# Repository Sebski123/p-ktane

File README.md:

# P-KTANE
## Sources
* https://github.com/dlareau/KTANE-physical
* https://imgur.com/gallery/J6HdM0v
* https://old.reddit.com/r/ktane/comments/a3fgyt/i_made_a_physical_version_of_the_video_game_keep/

run command `git config --local --add diff.fcinfo.textconv ./MiscCode/fcinfo` to use git diff on FreeCAD files

## ReDesign
### To-do
- [ ] Rewrite SWire protocol
- - [ ] Expand addressing (allow multiple of same module)
- - [ ] Don't need adress in packet
- - [ ] Don't to send 'ack' message (built into i2c)
- - [ ] Don't start and end messages (built into i2c)
- - [ ] Update sigrok decoder with new protocol
- [ ] Decide on module size
- [x] Add pinheaders to all schematics
- [ ] Figure out how to add battery/indicators
- [ ] Make symbol/footprint for arcade button
- [ ] Redo SimonSays schematic with above symbol
- [ ] Design PCBs
- [ ] Make more modules
- [x] Organize Repo
- [ ] Clean up README
- [x] Choose which modules to build
- [ ] Double check value of RSet for MAX7219 ICs
- [ ] Figure out how to add radio dial to MorseCode
- [ ] Modules on back?
- [ ] Add presets from KTANE?
- [ ] Variable amount of strikes?
- [ ] Use 14-segments for strike indicator?
- [ ] Better leaderboard?
- [ ] Way to enter name? (Password module?)
- [ ] Better system for swapping modules?
- [ ] Use HD107S for button module?
- [ ] Use built-in resistor to identify button?
- [ ] Implement Bounce2 in all button modules
- [ ] Add pullup resistors to I2C bus
- [ ] Make e-paper display
  - [x] Expose PSU enable pin
  - [x] Add SRAM IC
  - [x] Add microSD slot?
  - [ ] White image for storage
  - [ ] Add display/controller to GxEPD2?
- [ ] Figure out how to power device
  - [ ] Wired?
  - [ ] Battery?
  - [ ] Both?
- [ ] Add protection circuits?
  - [ ] Short circuit protection?
  - [ ] Overvoltage protection
    - [ ] Zener diode voltage clamp
  - [ ] Overcurrent protection
    - [x] Add polyfuse to every module
    - [ ] Measure curent draw for each module
- [ ] Add TMRpcm and SD to timer?
  - [ ] [This](https://maxoffsky.com/maxoffsky-blog/how-to-play-wav-audio-files-with-arduino-uno-and-microsd-card/)
  - [ ] Or [this](https://circuitdigest.com/microcontroller-projects/arduino-audio-music-player)

### v1 Compromises
| Module       | Problem                                              | Possible solution                              |
|--------------|------------------------------------------------------|------------------------------------------------|
| Button       | Text is separate from button instead of on top       | 3D-print text on button                        |
| Button       | Text is reduced to a single digit                    | Use changeable buttons with 3D-printed text    |
| Edgework     | Serial number is rough (16-segment display)          | Use E-paper display                            |
| Edgework     | All possible indicators are always present           | Use E-paper displays (expensive)               |
| Maze         | Hard to differentiate elements                       | Use RGB led's on PCB                           |
| Maze         | No way to see maze walls                             | Use 11x11 grid to also show walls              |
| Memory       | Press button under display instead of display itself | Place button under display and make it movable |
| Simon Says   | Rough sound                                          | Replace buzzer with proper speaker             |
| Simon Says   | Rough sound                                          | Replace tone() with better sine wave (filter?) |
| Simple wires | Wires are unplugged instead of cut                   | Use magnets to "cut" wires                     |

## Modules
| Module                                                       |Going to build| Coded | Schematic | PCB | Parts | Tested | Built | I2C addr.|
|--------------------------------------------------------------|--------------|-------|---------- |-----|-------|--------|-------|----------|
| Timer (Controller)                                           |      ✔️     |   🟡  |    🟡    |  ❌ |  ❌  |   ❌   |  ❌  |  MASTER  |
| Config (ESP8266)                                             |      ✔️     |   🟡  |    ✔️    |  ❌ |  ✔️  |   ✔️   |  ❌  |    0x1   |
| [Button](https://i.imgur.com/Leew7du.png)                    |      ✔️     |   ✔️  |    ✔️    |  ❌ |  ❌  |   ❌   |  ❌  |    0x2   |
| [Complicated Wires](https://i.imgur.com/jJb2Kp9.png)         |      ✔️     |   ✔️  |    ✔️    |  ❌ |  ❌  |   ❌   |  ❌  |    0x3   |
| [Maze](https://i.imgur.com/xXMdvLr.png)                      |      ✔️     |   🟡  |    ✔️    |  ❌ |  🟡  |   ❌   |  ❌  |    0x4   |
| [Memory](https://i.imgur.com/bvGt5gz.png)                    |      ✔️     |   🟡  |    ✔️    |  🟡 |  ❌  |   ❌   |  ❌  |    0x5   |
| [Morse Code](https://i.imgur.com/V4XAdVZ.png)                |      ✔️     |   ❌  |    🟡    |  ❌ |  ❌  |   ❌   |  ❌  |    0x6   |
| [Needy Capacitor Discharge](https://i.imgur.com/Q0VJkoo.png) |      ✔️     |   ✔️  |    ✔️    |  ❌ |  ❌  |   ❌   |  ❌  |    0x7   |
| [Needy Knob](https://i.imgur.com/hlpkEUD.png)                |      ✔️     |   ✔️  |    ✔️    |  ❌ |  ❌  |   ❌   |  ❌  |    0x8   |
| [Needy Venting Gas](https://i.imgur.com/f2eua3p.png)         |      ✔️     |   ✔️  |    ✔️    |  ❌ |  ❌  |   ❌   |  ❌  |    0x9   |
| [Password](https://i.imgur.com/us0XRBs.png)                  |      ✔️     |   ❌  |    ✔️    |  ❌ |  ❌  |   ❌   |  ❌  |    0xA   | 
| [Simon Says](https://i.imgur.com/uX7BzED.png)                |      ✔️     |   🟡  |    ✔️    |  ❌ |  ❌  |   ❌   |  ❌  |    0xB   |
| [Simple Wires](https://i.imgur.com/xLXpCYH.png)              |      ✔️     |   🟡  |    ✔️    |  ❌ |  ❌  |   ❌   |  ❌  |    0xC   |
| [Keypads](https://i.imgur.com/Zy6ScEo.png)                   |      ❌     |   ❌  |    ❌    |  ❌ |  ❌  |   ❌   |  ❌  |    N/A   |
| [Who's on First](https://i.imgur.com/YisE1go.png)            |      ❌     |   ❌  |    ❌    |  ❌ |  ❌  |   ❌   |  ❌  |    N/A   |
| [Wire Sequence](https://i.imgur.com/1drzKTO.png)             |      ❌     |   ❌  |    ❌    |  ❌ |  ❌  |   ❌   |  ❌  |    N/A   |

# How to burn bootloader and upload sketches for ATMega328
## How to burn bootloader
### Install boards
1. Open the Arduino IDE.
1. Open the **File > Preferences** menu item.
1. Enter the following URL in **Additional Boards Manager URLs**:

    ```
    https://mcudude.github.io/MiniCore/package_MCUdude_MiniCore_index.json
    ``` 

1. Open the **Tools > Board > Boards Manager...** menu item.
1. Wait for the platform indexes to finish downloading.
1. Scroll down until you see the **MiniCore** entry and click on it.
1. Click **Install**.
1. After installation is complete close the **Boards Manager** window.
1. **Note**: If you plan to use the *PB series, you need the latest version of the Arduino toolchain. This toolchain is available through IDE 1.8.6 or newer. Here's how you install/enable the toolchain:
  -  Open the **Tools > Board > Boards Manager...** menu item.
  -  Wait for the platform indexes to finish downloading.
  -  The top is named **Arduino AVR boards**. Click on this item.
  -  Make sure the latest version is installed and selected
  -  Close the **Boards Manager** window.

### Prepare Arduino
1. Copy [this](https://raw.githubusercontent.com/adafruit/ArduinoISP/master/ArduinoISP.ino) code into the Arduino IDE and upload it to an Arduino normally.
1. Connect Arduino to the ATMega as shown below (Capacitor is important).

### Burn bootloader
1. Select the **Tools > Board > ATmega328** menu item from the MiniCore section.
1. Select the **Tools > Variant > 328 / 328A** menu item.
1. Select the **Tools > Clock > Internal 8MHz** menu item.
1. Select the **Tools > Programmer > Arduino as ISP** menu item.
1. Click **Tools > Burn Bootloader**

## How to upload sketches
### Wiring
1. Remove ATmega328 from Arduino
1. Connect Arduino to the ATMega as shown below.

### Uploading
1. Select the **Tools > Board > ATmega328** menu item from the MiniCore section.
1. Select the **Tools > Variant > 328 / 328A** menu item.
1. Select the **Tools > Clock > Internal 8MHz** menu item.
1. Select the **Tools > Programmer > Arduino as ISP** menu item.
1. Click Upload.

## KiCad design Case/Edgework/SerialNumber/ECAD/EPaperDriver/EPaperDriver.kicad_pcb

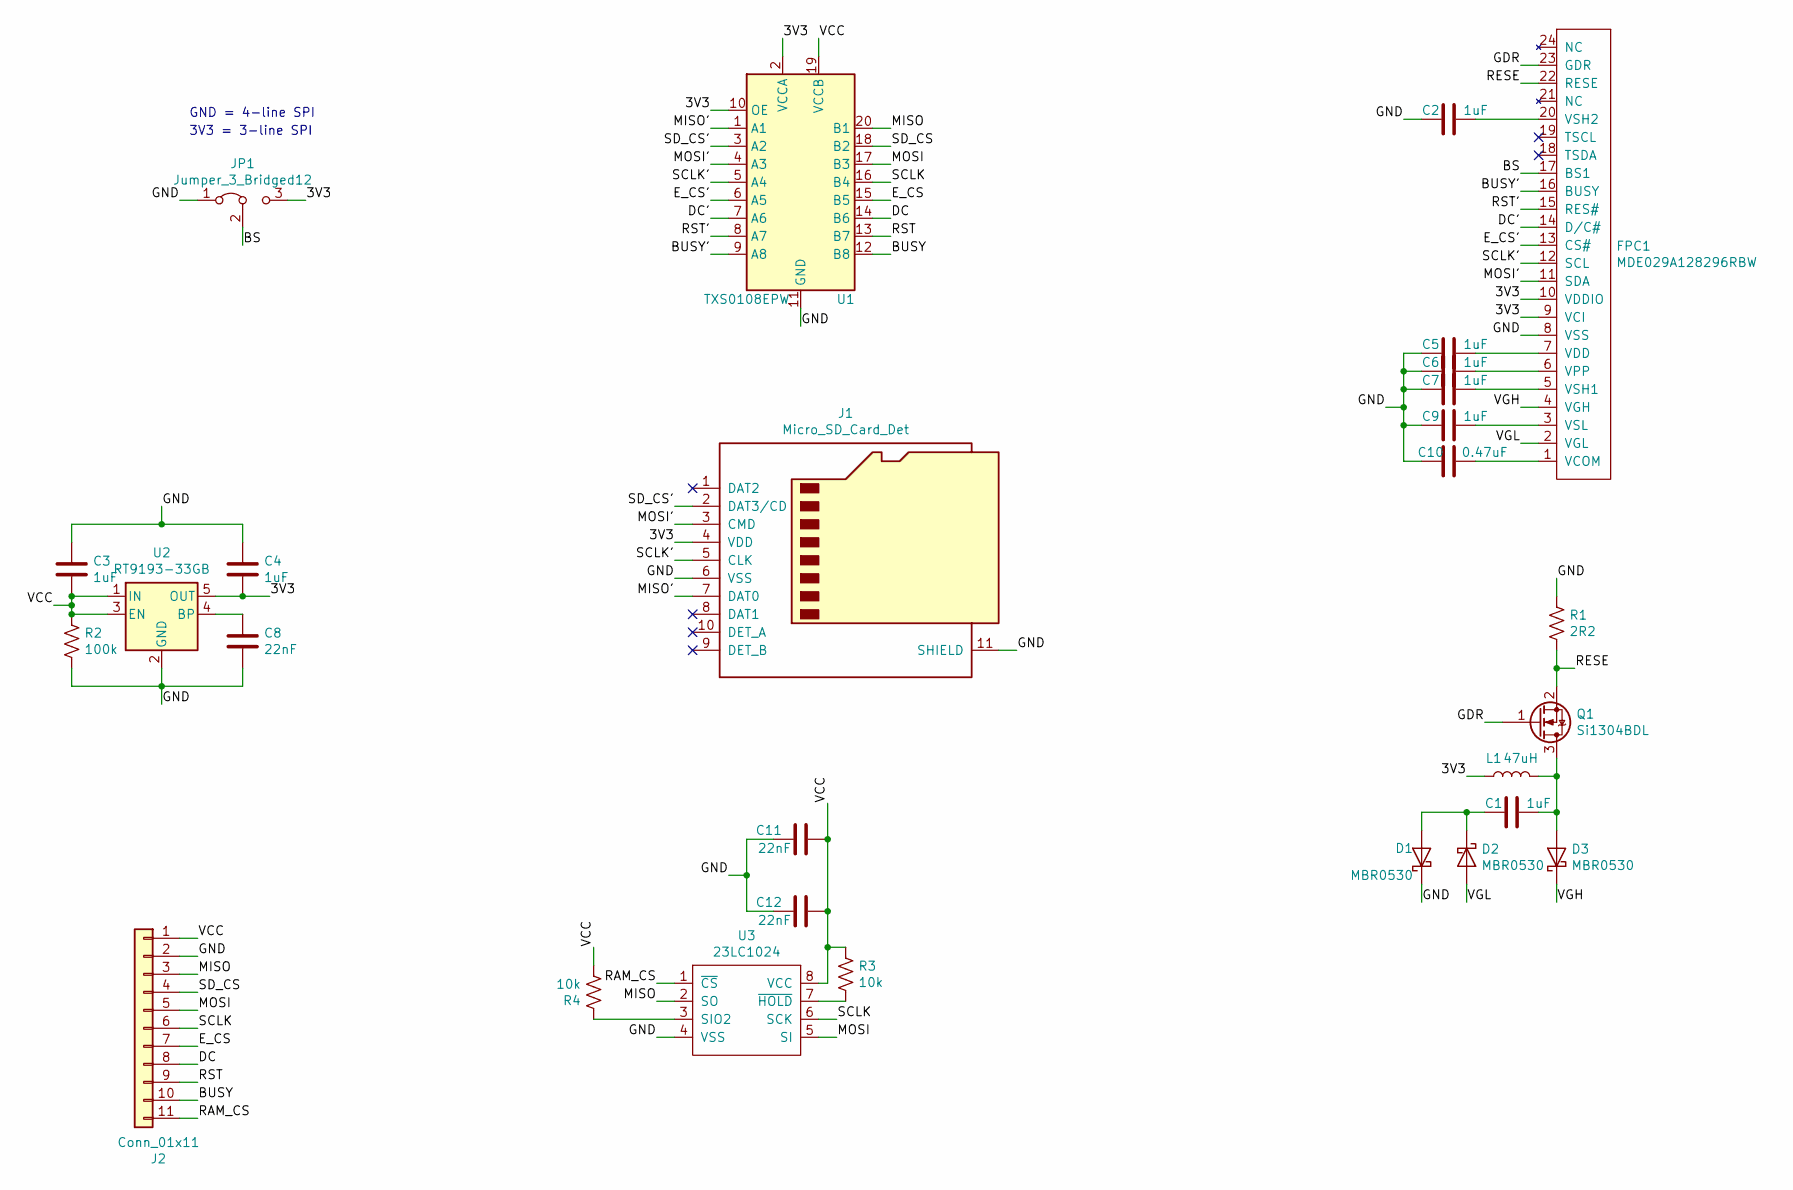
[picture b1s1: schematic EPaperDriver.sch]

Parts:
C1, C2, C3, C4, C5, C6, C7, C9: 1uF; C_0805_2012Metric_Pad1.15x1.40mm_HandSolder
C8, C11, C12: 22nF; C_0805_2012Metric_Pad1.15x1.40mm_HandSolder
C10: 0.47uF; C_0805_2012Metric_Pad1.15x1.40mm_HandSolder
D1, D2, D3: MBR0530; D_SOD-123
FPC1: MDE029A128296RBW; Hirose_FH12-24S-0.5SH_1x24-1MP_P0.50mm_Horizontal
J1: Micro_SD_Card_Det; microSD_HC_Hirose_DM3D-SF
J2: Conn_01x11; PinHeader_1x11_P2.54mm_Vertical
JP1: Jumper_3_Bridged12; SolderJumper-3_P1.3mm_Open_Pad1.0x1.5mm
L1: 47uH; L_12x12mm_H6mm
Q1: Si1304BDL; SOT-323_SC-70
R1: 2R2; R_0805_2012Metric_Pad1.15x1.40mm_HandSolder
R2: 100k; R_0805_2012Metric_Pad1.15x1.40mm_HandSolder
R3, R4: 10k; R_0805_2012Metric_Pad1.15x1.40mm_HandSolder
U1: TXS0108EPW; TSSOP-20_4.4x6.5mm_P0.65mm
U2: RT9193-33GB; SOT-23-5
U3: 23LC1024; SOIC-8_3.9x4.9mm_P1.27mm

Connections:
/3V3: C4.2, FPC1.9 (VCI), FPC1.10 (VDDIO), J1.4 (VDD), JP1.3 (B), L1.1, U1.2 (VCCA), U1.10 (OE), U2.5 (OUT)
/BS: FPC1.17 (BS1), JP1.2 (C)
/BUSY: J2.10, U1.12 (B8)
/BUSY': FPC1.16 (BUSY), U1.9 (A8)
/DC: J2.8, U1.14 (B6)
/DC': FPC1.14 (D/C#), U1.7 (A6)
/E_CS: J2.7, U1.15 (B5)
/E_CS': FPC1.13 (CS#), U1.6 (A5)
/GDR: FPC1.23 (GDR), Q1.1 (G)
/GND: C2.1, C3.1, C4.1, C5.1, C6.1, C7.1, C8.2, C9.1, C10.1, C11.1, C12.1, D1.1 (K), FPC1.8 (VSS), J1.6 (VSS), J1.11 (SHIELD), J2.2, JP1.1 (A), R1.1, R2.2, U1.11 (GND), U2.2 (GND), U3.4 (VSS)
/MISO: J2.3, U1.20 (B1), U3.2 (SO)
/MISO': J1.7 (DAT0), U1.1 (A1)
/MOSI: J2.5, U1.17 (B3), U3.5 (SI)
/MOSI': FPC1.11 (SDA), J1.3 (CMD), U1.4 (A3)
/RAM_CS: J2.11, U3.1 (~CS~)
/RESE: FPC1.22 (RESE), Q1.2 (S), R1.2
/RST: J2.9, U1.13 (B7)
/RST': FPC1.15 (RES#), U1.8 (A7)
/SCLK: J2.6, U1.16 (B4), U3.6 (SCK)
/SCLK': FPC1.12 (SCL), J1.5 (CLK), U1.5 (A4)
/SD_CS: J2.4, U1.18 (B2)
/SD_CS': J1.2 (DAT3/CD), U1.3 (A2)
/VCC: C3.2, C11.2, C12.2, J2.1, R2.1, R3.1, R4.2, U1.19 (VCCB), U2.1 (IN), U2.3 (EN), U3.8 (VCC)
/VGH: D3.1 (K), FPC1.4 (VGH)
/VGL: D2.2 (A), FPC1.2 (VGL)
unnamed: C1.1, D3.2 (A), L1.2, Q1.3 (D)
unnamed: C1.2, D1.2 (A), D2.1 (K)
unnamed: C2.2, FPC1.20 (VSH2)
unnamed: C5.2, FPC1.7 (VDD)
unnamed: C6.2, FPC1.6 (VPP)
unnamed: C7.2, FPC1.5 (VSH1)
unnamed: C8.1, U2.4 (BP)
unnamed: C9.2, FPC1.3 (VSL)
unnamed: C10.2, FPC1.1 (VCOM)
unnamed: R3.2, U3.7 (~HOLD~)
unnamed: R4.1, U3.3 (SIO2)

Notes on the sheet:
GND = 4-line SPI
3V3 = 3-line SPI

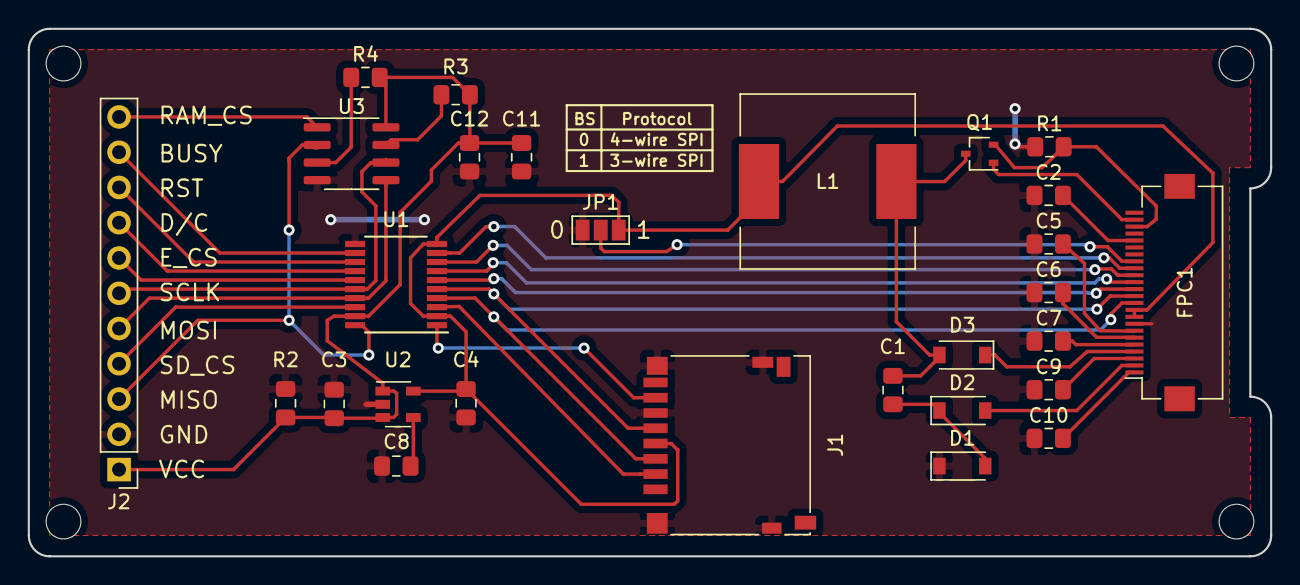
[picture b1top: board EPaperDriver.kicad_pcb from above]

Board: 4 copper layers, 89.5 x 38.0 mm, 28 parts (0 on the bottom side), 36 nets.

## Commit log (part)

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2019-08-02 Moved and renamed some files
2019-08-02 Added updated .ino file
2019-08-02 Fixed typo
2019-08-02 Started work on maze code
2019-08-05 Fixed win/lose condition
2019-08-05 Added config module code
2019-08-05 Made strikes and clear LED work + serial from ESP
2019-08-05 Renamed folder
2019-08-06 Updated missing parts list
2019-08-12 Added names to some of the components
2019-08-15 Fixing some pin numbers
2019-08-15 Finished maze Module schematic
2020-04-02 Added Arduino config
2020-04-02 Added basic wires module
2020-04-02 Rename files
2020-04-02 Added SimonSays 3d files
2020-04-02 Fixed includes
2020-04-02 Added functionality for modules to get time from controller
2020-04-02 Added button module
2020-04-06 Added some logging for debugging
2020-04-06 Added prebuild task
2020-04-07 Made code match schematics
2020-04-08 Added part file for button base
2020-04-08 Added part file for button middle
2020-04-08 Fix css on setup page
2020-04-08 Fixed formatting and added some debug messages
2020-04-08 Fixed formatting and added debugging via. SWSerial
2020-04-09 Added template for module face plate
2020-04-09 Added prototype for button face plate, not finalized yet
2020-04-09 Added section for Burning bootloader and uploading sketches
2020-04-10 Updated face plate, added ring part. Still need to make outer case for button
2020-04-11 Added spreadsheet for calculating expenses
2020-04-12 Fixed issue of dest_time overflowing
2020-04-12 Remove NeoICSerial Module
2020-04-12 Get newest commit from NeoICSerial
2020-04-12 Now keeps showing time left when bomb is solved
2020-04-12 Export schematic as pdf
2020-04-12 Revert "Added frames to all modules"
    This reverts commit 3eabf43de3682e49b345895a8346113ada920e34
2020-04-14 Modified existing face plates with wider spacings
2020-04-14 Added face plate for memory module, buttons included
2020-04-22 Changed wire face plate to the correct file
2020-04-22 changed button face plate to correct file
2020-04-26 Added missing step in upload guide
2020-04-26 Fixed issue with red and black wires being swaped and added more logging
2020-04-29 Added finished design of box
2020-04-29 Added solidworks files for each box part
2020-04-29 Updated wire face plate with larger holes
2020-04-29 Added assembly for box
2020-04-30 Added corner piece to box and updated the assembly
2020-04-30 Added new submodule for controlling a MAX6954 LED driver
2020-04-30 Added python script for decoding DSerial packages
2020-04-30 Updated schematic
2020-05-02 Added display for serial number and renamed some variables
2020-05-02 Updated MAX6954 lib
2020-05-05 Added main module face plate and speaker grill
2020-05-05 Added file for button face plate side bar
2020-05-06 Removed old 7-segment code
2020-05-11 difference got paid
2020-05-11 prebuild script should now work on other pc's
2020-05-11 Fixed red and black being swapped and added some logging
2020-05-11 Update to show what it should look like
2020-05-11 Added client number to maze module
2020-05-13 Added face plate for maze module
2020-05-14 Changed varable types to save memory
2020-05-14 Added some logging
2020-05-14 Added even more logging
2020-05-14 Moved a bunch of strings to progmem to save memory
2020-05-14 Added debounceing to buttons
2020-05-14 moved led logic inside main loop
2020-05-14 fixed formatting
2020-05-14 Updated website to support wire generation
2020-05-14 Updated maze module face plate with bigger spacings
2020-05-17 Added code for rgb leds and finished module logic
2020-05-17 Change schematic to accurately reflect how clear leds work
2020-05-18 Added buzzer to simon says module
2020-05-18 Added buzzer code to simon says
2020-05-20 Simon says will now get config from main module
2020-05-20 Switched to using LedControl lib for memory module
2020-05-20 Added some loging
2020-05-20 Fixed buttons being inverted
2020-05-20 Swapped "up" and "left" buttons
2020-05-20 Removed infinite loop that prevented module from being restarted
2020-05-21 Updated button base to have replacable legs
2020-05-21 Added files for button module support
2020-05-21 Updated modules to use SWire
2020-05-21 Started updating mainModule to use SWire
2020-05-21 Started updating KTANECommon to use SWire
2020-05-21 Update prebuild script
2020-05-22 Removed unused functions and added some logging
2020-05-22 Removed unused variables
2020-05-22 Now client at least gets config
2020-05-24 Added a bit of logging
2020-05-24 Updated I2C events for SWireClient
2020-05-24 Update identifyClients to only accept ACK as valid
2020-05-24 Add function to check for incoming messages from slaves
2020-05-24 Removed 'Y' as a possible character for serial nr to match game
2020-05-24 Now only pools clients every 100 ms
2020-05-24 Added an exception for incoming data
2020-05-25 Added functionality to free up memory
2020-05-25 Removed logging from lib
2020-05-25 Changed logging for maze module
2020-05-25 Updated maze module pins for I2C
2020-05-25 Updated simon says module pins for I2C
2020-05-25 Updated memory module pins for I2C
2020-05-25 Updated button module pins for I2C
2020-05-25 Fixed issue with display not clearing
2020-05-25 Update formatting
2020-05-25 Removed NeoICSerial lib
2020-05-25 Wires module now uses external ADC(MCP3008)
2020-05-25 Added logging for memory
2020-05-25 Updated modules for I2C and added external ADC for wires module
2020-05-25 Swapped 2 pins and added mising class init
2020-05-25 Changed submodule urls to use SSH
2020-05-25 Added Adafruit_MCP3008 lib as submodule
2020-05-25 Removed useless code
2020-05-25 Removed comment and added logging
2020-05-26 updated pillar for button holder
2020-05-26 Updated spacings for memory module face plate
2020-05-26 Update PDF with I2C schematic
2020-05-26 Added power connections for wires module
2020-05-26 Tweaked values for external ADC
2020-05-26 Added char escape for null char
2020-05-26 Added connection betwen main module and config module
2020-05-26 Removed extra '|'
2020-05-26 Fixed 2 swapped functions
2020-05-26 Increased length of stem
2020-05-26 Added part for a button holder for memory module
2020-05-27 Made logging more verbose for incomming messages
2020-05-27 Fix formatting
2020-05-27 Swapped buttons 3 and 4
2020-05-27 Uncommented test stuff
2020-05-28 Renamed simon says buttons
2020-05-29 Update MAX6954 submodule
2020-05-29 Swapped 2 pins on MAX6954 IC for readability
2020-06-01 Added template module
2020-06-01 Update submodule
2020-06-01 Fixed speaker pin being wrong
2020-06-01 Goal can no longer appear on marker locations
2020-06-05 Updated to work onESP32
2020-06-05 Updated schematic for report
2020-06-06 Fixed wires module
2020-06-07 Renamed function arguments and added function prototype
2020-06-07 Added some defines for clarity
2020-06-07 Added some logging for debuging
2020-06-07 Now properly detects when button has been held
2020-06-08 Added code for displaying millisecons
2020-06-08 Now sets all clock digits to 0
2020-06-08 Now actually displays 0's on loose
2020-06-08 Added timeout when waiting for time from main module
2020-06-08 Switched to analogWrite for better colors
2020-06-09 Fixed part being different from manual
2020-06-10 Added submodule for MCP23017 lib
2020-06-11 Added MCP23017 to schematic
2020-06-11 Added resistors to indicator led's
2020-06-11 Added code for supporting batteries and indicators
2020-06-11 Now waits for serial to be ready instead of set amount of time
2020-06-12 Added simulator for predicting solutions for all modules
2020-06-12 Buton now takes into account batteries and lit indicators
2020-06-13 Added comment
2020-06-13 Commented out unused code
2020-06-13 Can now send scores to firebase
2020-06-13 Now sends time left to ESP on win
2020-06-14 Add .gitignore entries for Firebase
2020-06-14 Fixed error on no batteries
2020-06-28 Fixed wrong comment
2020-06-28 Updated simulator
2020-08-06 Moved some stuff around
2020-08-06 Added schematic to each individual module
2020-08-06 Update prebuild task
2020-10-19 Added Adafruit_LiquidCrystal as submodule for controlling LCDs
2020-10-19 Converted button schematic to KiCad
2020-10-19 Converted config schematic to KiCad
2020-10-19 Converted simonSays schematic to KiCad
2020-10-19 Converted simpleWires schematic to KiCad
2020-10-19 Added complicatedWires schematic
2020-10-19 Added morseCode schematic
2020-10-19 Added NeedyKnob schematic
2020-10-19 Added password schematic
2020-10-19 Converted maze schematic to KiCad and swapped single color leds with RGB ones
2020-10-19 Added some update reminders
2020-10-19 Activated internal pullup resistors for buttons
2020-10-19 Added some placeholder files
2020-10-19 Updated what arduino.json should look like
2020-10-19 Added code for ComplicatedWires
2020-10-19 Added function to handle needy modules
2020-10-19 Added code for NeedyCapacitorDischarge
2020-10-19 Added code for NeedyKnob
2020-10-19 Updated .gitignore
2020-10-19 Removed some submodules
2020-10-21 Added some more stuff to the To-Do list
2020-10-21 Removed unused labels
2020-10-21 Added some items to to-do list
2020-10-22 Added polyfuses to all modules
2020-11-03 Updated maze code to use HD107S leds
2020-11-03 Updated value of Rset for MAX7219
2020-11-03 Updated To-Do list
2020-11-03 Updated module progress table
2020-12-03 Added tool to see diff of .FCStd files
2020-12-03 Added cad file for a simon says arcade button
2020-12-03 Added graphics information to Arcade button
2020-12-04 Added instruction to readme
2020-12-07 Added missing setCursor call
2020-12-07 Updated EPaper driver
2020-12-28 Added VGA, DVI, and Parallel port 3D models
2021-01-30 Added item to checklist
2021-01-30 Fixed error with type mismatch
2021-01-30 Fixed bargraph algorithm
2021-01-30 Rewrote weird logic
2021-01-30 Increase update frequency
2021-01-30 Now updates countdown every update
2021-01-30 Added PS/2 & RJ45 ports
2021-01-30 Update arduino config
2021-02-01 Moved some stuff around and removed a random() call
2021-02-01 Now also stops needy modules on loss
2021-02-05 Added sigrok decoder
2021-02-05 Update to-do list
2021-02-07 Renamed a bunch of files to allow adding header files
2021-05-25 Made schematic for edgeWorkController
2021-05-25 Small changes to ktaneCommon
2021-05-30 Reduced size of config type
2021-05-30 Added functionality to send seed to clients
2021-05-30 Added reset exeption for widget controller
2021-05-30 Updated timer schematic
2021-06-03 Update "settings" type
2021-06-03 Decresed EDP buffer size to avoid OOM errors
2021-06-03 Now gets a seed for "random" from the master
2021-06-03 Now sends a completed config back to master
2021-06-04 Change how "timeLeft" is sent to modules
    This should reduce the amount of calculations done on master
2021-06-04 Update imports
2021-06-04 Updated variables
2021-06-04 Temporarily disable playMelody function
    This will be replaced with the DFPlayer lib later
2021-06-04 Change how the config is obtained
    Timer now recives settings from ESP rather than a full config
    This allows the config to be generated on the widget controller instead of the timer
2021-06-04 Move some stuff in setup around
2021-06-04 Moved clock managment to it's own function
2021-06-04 Added some stuff to make it easier to test
2021-06-05 Added DFPlayer functionality
2021-06-05 Now should play beep sound every second
2021-06-13 KiCad version update
2021-06-13 Fixed config message length
2021-06-13 Added pullup resistors to I2C lines
    Also add resistor for clock dot
2021-06-13 Added required functions to notify class
2021-06-13 Exchanged fake strike system with the real one
2021-06-13 Added a win condition
2021-06-16 MorseCode: Formatting
2021-06-16 Timer: Detect and reset modules earlier
    This is to allow widget controller to be reset by timer
2021-06-16 Timer: Only turn clock colon on if necessary
2021-06-16 MorseCode: Added motor to schematic
    This small motor will be used to show frequency with a physical marker
2021-06-16 KTANECommon: Also send reset to widget controller
